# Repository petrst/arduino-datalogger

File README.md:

Moved under https://bitbucket.org/petrst/celsius project

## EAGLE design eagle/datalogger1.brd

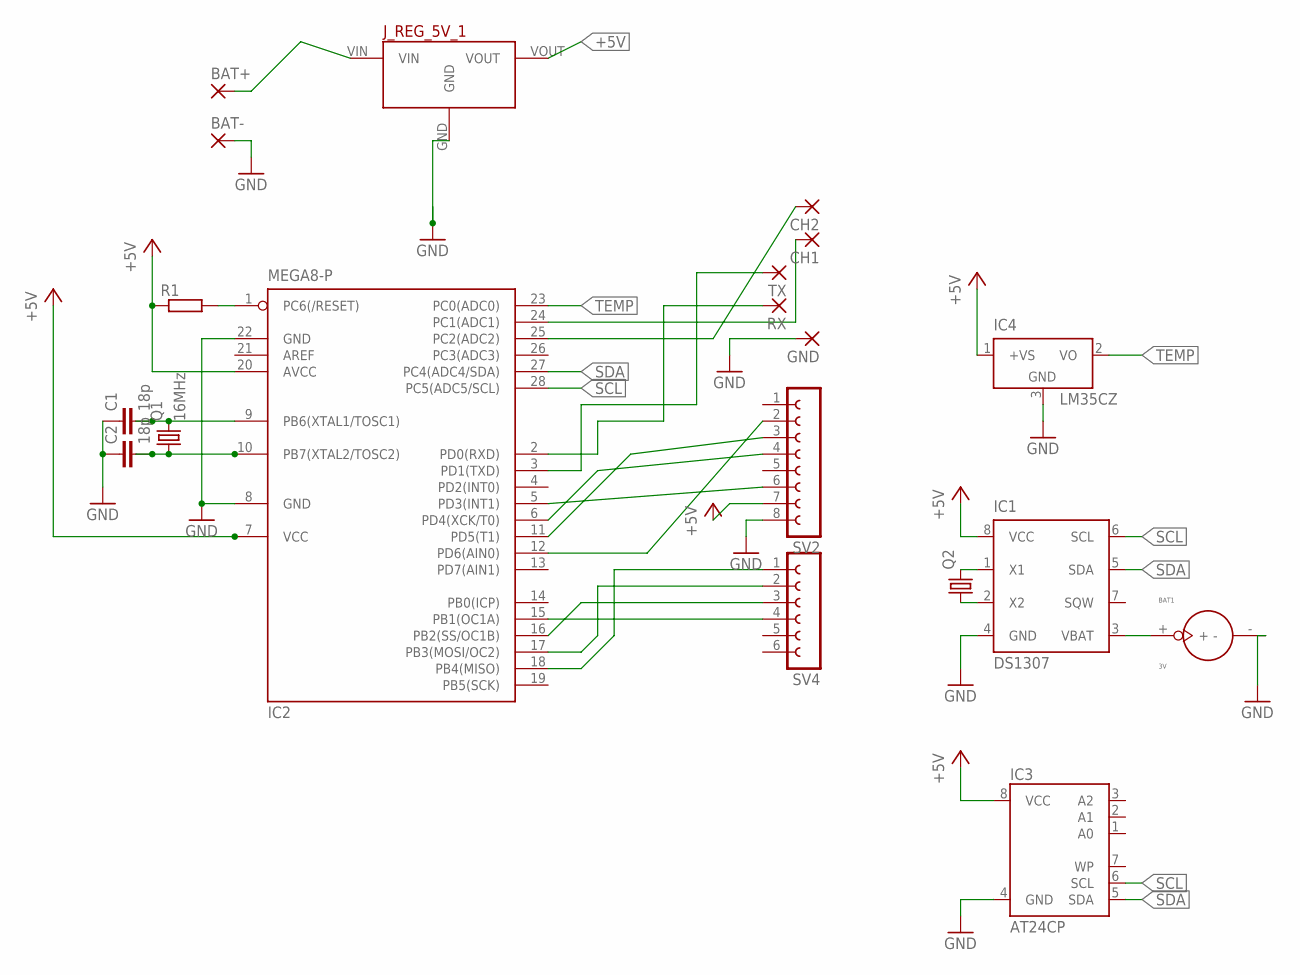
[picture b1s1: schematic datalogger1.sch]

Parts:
BAT1: 3V; BATTERY_1236_C
BAT+: 2,54/1,0
BAT-: 2,54/1,0
C1, C2: 18p; C050-024X044
CH1, CH2: 1,6/0,8
GND: 1,6/0,8
IC1: DS1307; DIL08
IC2: MEGA8-P; DIL28-3
IC3: AT24CP; DIL08
IC4: LM35CZ; TO92
J_REG_5V_1: 5V_VOLTAGE_REGULATOR
Q1: 16MHz; HC49/S
Q2: CRYSTALTC38H; TC38H
R1: R-EU_0204/7; 0204/7
RX: 1,6/0,8
SV2: FE08-1; FE08
SV4: FE06-1; FE06
TX: 1,6/0,8

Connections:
+5V: IC1.8 (VCC), IC2.7 (VCC), IC2.20 (AVCC), IC3.8 (VCC), IC4.1 (+VS), J_REG_5V_1.VOUT, R1.1, SV2.7
GND: BAT1.-, BAT-.1, C1.1, C2.1, GND.1, IC1.4 (GND), IC2.8 (GND), IC2.22 (GND), IC3.4 (GND), IC4.3 (GND), J_REG_5V_1.GND, SV2.8
unnamed: IC1.1 (X1), Q2.2
unnamed: IC1.2 (X2), Q2.1
unnamed: C1.2, IC2.9 (PB6(XTAL1/TOSC1)), Q1.2
unnamed: C2.2, IC2.10 (PB7(XTAL2/TOSC2)), Q1.1
unnamed: IC2.18 (PB4(MISO)), SV4.1
unnamed: IC2.17 (PB3(MOSI/OC2)), SV4.2
unnamed: BAT1.+, IC1.3 (VBAT)
unnamed: IC2.16 (PB2(SS/OC1B)), SV4.3
unnamed: IC2.15 (PB1(OC1A)), SV4.4
unnamed: IC2.12 (PD6(AIN0)), SV2.2
unnamed: IC2.11 (PD5(T1)), SV2.3
unnamed: IC2.6 (PD4(XCK/T0)), SV2.4
unnamed: IC2.5 (PD3(INT1)), SV2.6
unnamed: IC2.1 (PC6(/RESET)), R1.2
unnamed: IC2.2 (PD0(RXD)), RX.1
unnamed: IC2.3 (PD1(TXD)), TX.1
unnamed: CH1.1, IC2.24 (PC1(ADC1))
unnamed: BAT+.1, J_REG_5V_1.VIN
unnamed: CH2.1, IC2.25 (PC2(ADC2))
SCL: IC1.6 (SCL), IC2.28 (PC5(ADC5/SCL)), IC3.6 (SCL)
SDA: IC1.5 (SDA), IC2.27 (PC4(ADC4/SDA)), IC3.5 (SDA)
TEMP: IC2.23 (PC0(ADC0)), IC4.2 (VO)

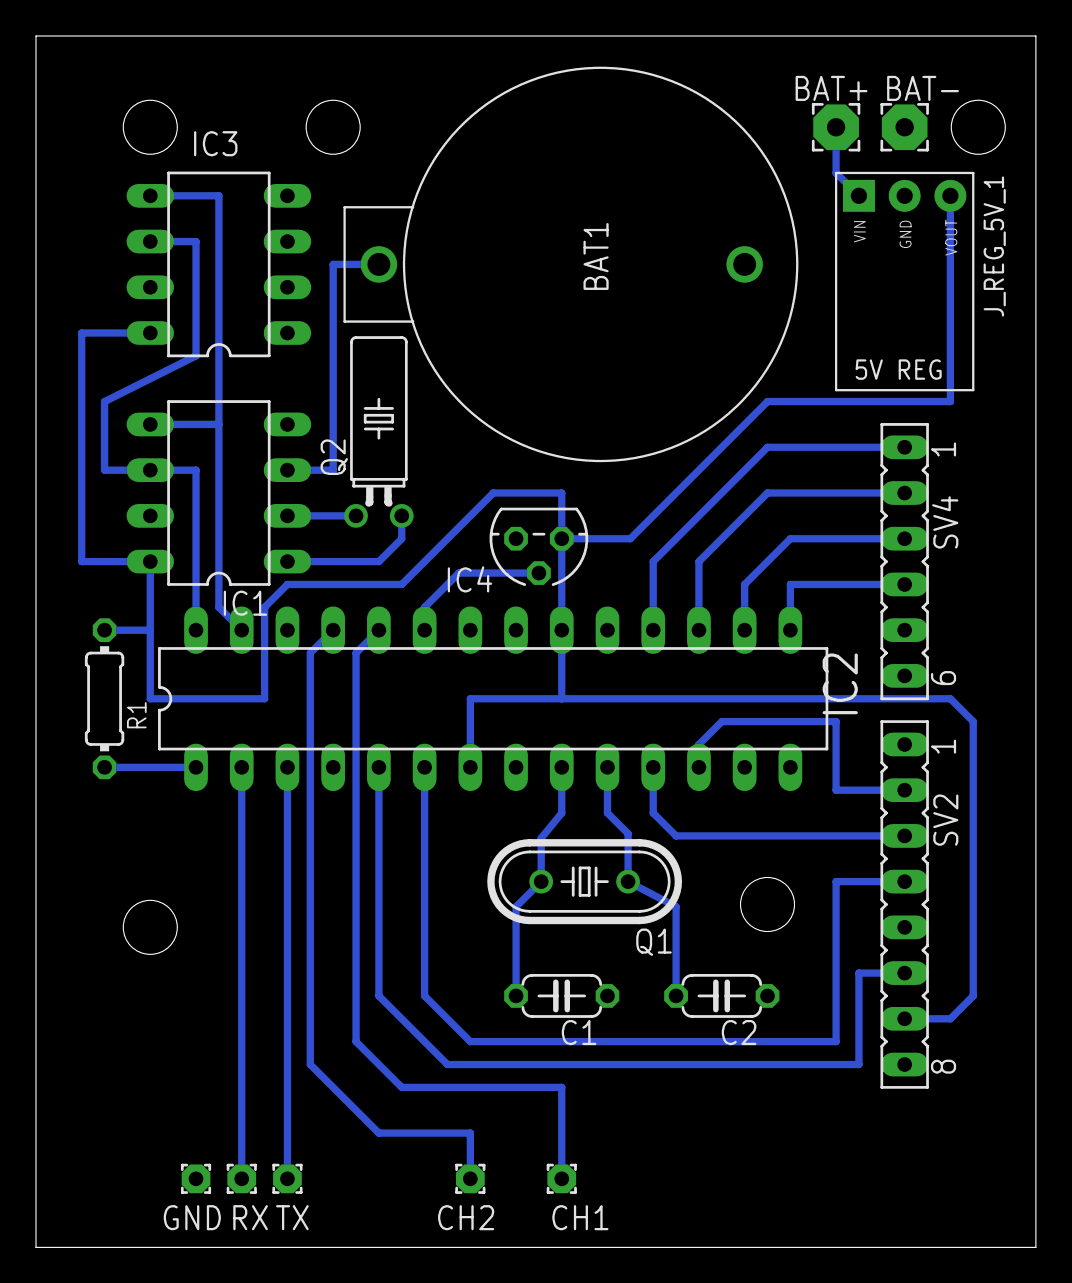
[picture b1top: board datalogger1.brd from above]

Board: 2 copper layers, 55.5 x 67.3 mm, 20 parts (0 on the bottom side), 24 nets.

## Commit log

2016-03-28 Tubning for external board
2016-03-28 Interrupt number corrected
2016-03-28 Missing files added
2016-03-29 libraries added
2016-03-29 Innterrupt pins number corrected
2016-04-01 EAGLE project added
2016-04-04 Another change in pin mapping. Cleaning and python tool
2016-04-06 Repeat write to EEPROM when fails. Sync date.
2018-01-21 README.md created online with Bitbucket
